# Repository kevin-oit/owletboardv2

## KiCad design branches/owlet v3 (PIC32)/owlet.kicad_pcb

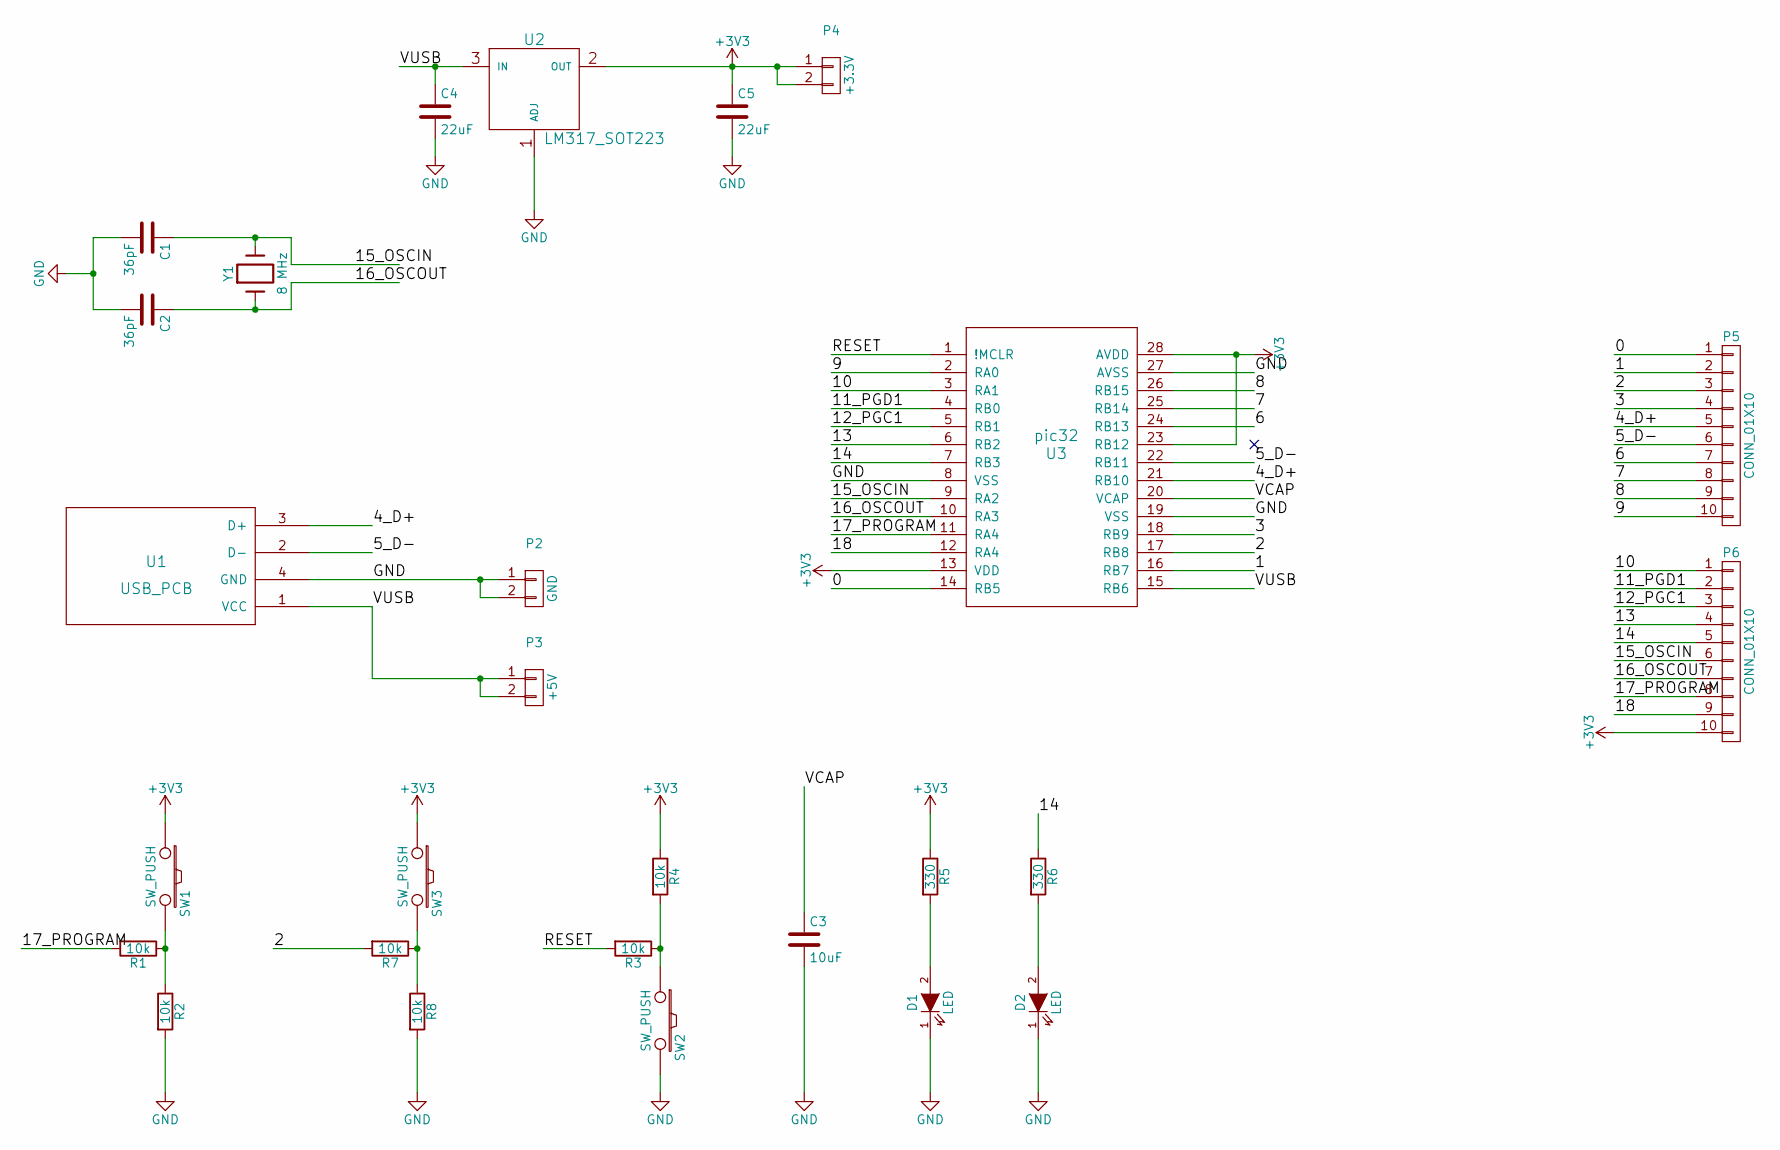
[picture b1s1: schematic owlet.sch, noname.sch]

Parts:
C1, C2: 36pF; C_Disc_D3_P2.5
C3: 10uF; C_Disc_D3_P2.5
C4, C5: 22uF; C_Disc_D3_P2.5
D1, D2: LED; LED-5MM
P2: GND; Pin_Header_Straight_1x02
P3: +5V; Pin_Header_Straight_1x02
P4: +3.3V; Pin_Header_Straight_1x02
P5, P6: CONN_01X10; Pin_Header_Straight_1x10
R1, R2, R3, R4, R7, R8: 10k; Resistor_Vertical_RM5mm
R5, R6: 330; Resistor_Vertical_RM5mm
SW1, SW2, SW3: SW_PUSH; SW_PUSH_SMALL
U1: USB_PCB; pcb_usb
U2: LM317_SOT223; SOT-223
U3: pic32; DIP-28_W7.62mm
Y1: 8 MHz; Crystal_HC49-U_Vertical

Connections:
+3V3: C5.1, P4.1, P4.2, P6.10, R4.1, R5.1, SW1.1, SW3.1, U2.2 (OUT), U3.13 (VDD), U3.23 (RB12), U3.28 (AVDD)
/0: P5.1, U3.14 (RB5)
/1: P5.2, U3.16 (RB7)
/2: P5.3, R7.2, U3.17 (RB8)
/3: P5.4, U3.18 (RB9)
/4_D+: P5.5, U1.3 (D+), U3.21 (RB10)
/5_D-: P5.6, U1.2 (D-), U3.22 (RB11)
/6: P5.7, U3.24 (RB13)
/7: P5.8, U3.25 (RB14)
/8: P5.9, U3.26 (RB15)
/9: P5.10, U3.2 (RA0)
/10: P6.1, U3.3 (RA1)
/11_PGD1: P6.2, U3.4 (RB0)
/12_PGC1: P6.3, U3.5 (RB1)
/13: P6.4, U3.6 (RB2)
/14: P6.5, R6.1, U3.7 (RB3)
/15_OSCIN: C1.1, P6.6, U3.9 (RA2), Y1.2
/16_OSCOUT: C2.1, P6.7, U3.10 (RA3), Y1.1
/17_PROGRAM: P6.8, R1.2, U3.11 (RA4)
/18: P6.9, U3.12 (RA4)
/RESET: R3.2, U3.1 (!MCLR)
/VCAP: C3.1, U3.20 (VCAP)
/VUSB: C4.1, P3.1, P3.2, U1.1 (VCC), U2.3 (IN), U3.15 (RB6)
GND: C1.2, C2.2, C3.2, C4.2, C5.2, D1.1 (K), D2.1 (K), P2.1, P2.2, R2.2, R8.2, SW2.2, U1.4 (GND), U2.1 (ADJ), U3.8 (VSS), U3.19 (VSS), U3.27 (AVSS)
unnamed: D1.2 (A), R5.2
unnamed: D2.2 (A), R6.2
unnamed: R1.1, R2.1, SW1.2
unnamed: R3.1, R4.2, SW2.1
unnamed: R7.1, R8.1, SW3.2

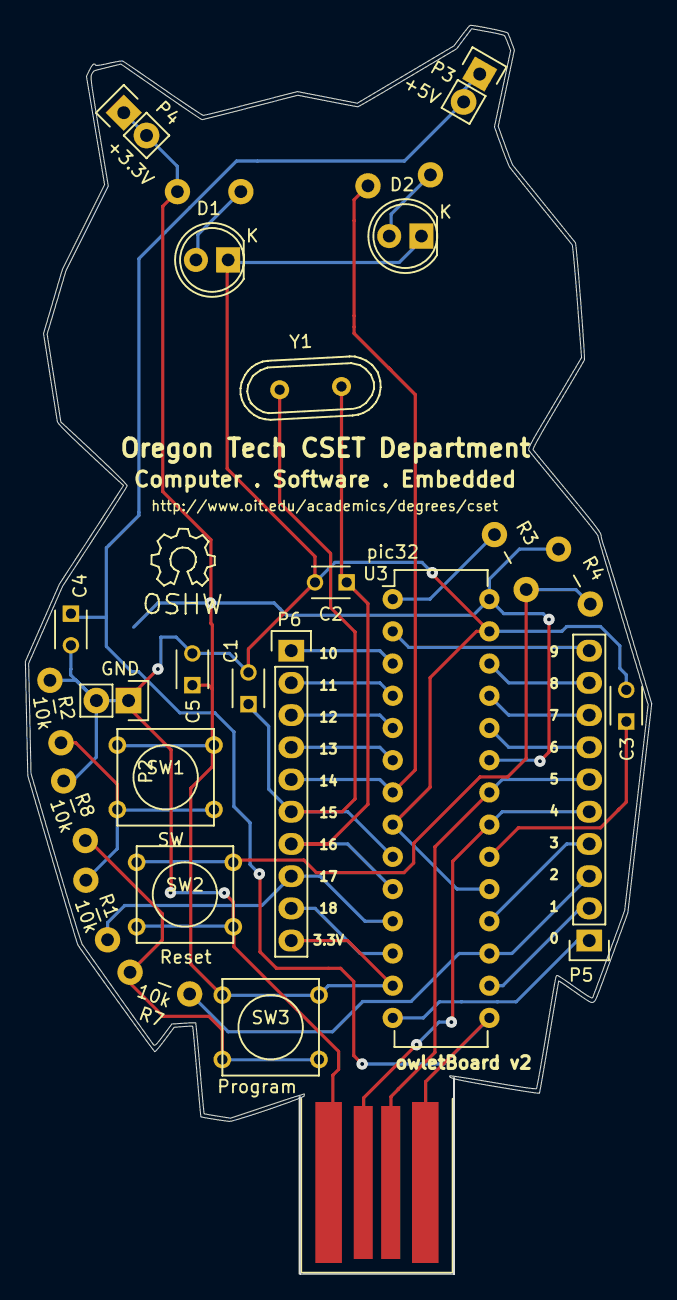
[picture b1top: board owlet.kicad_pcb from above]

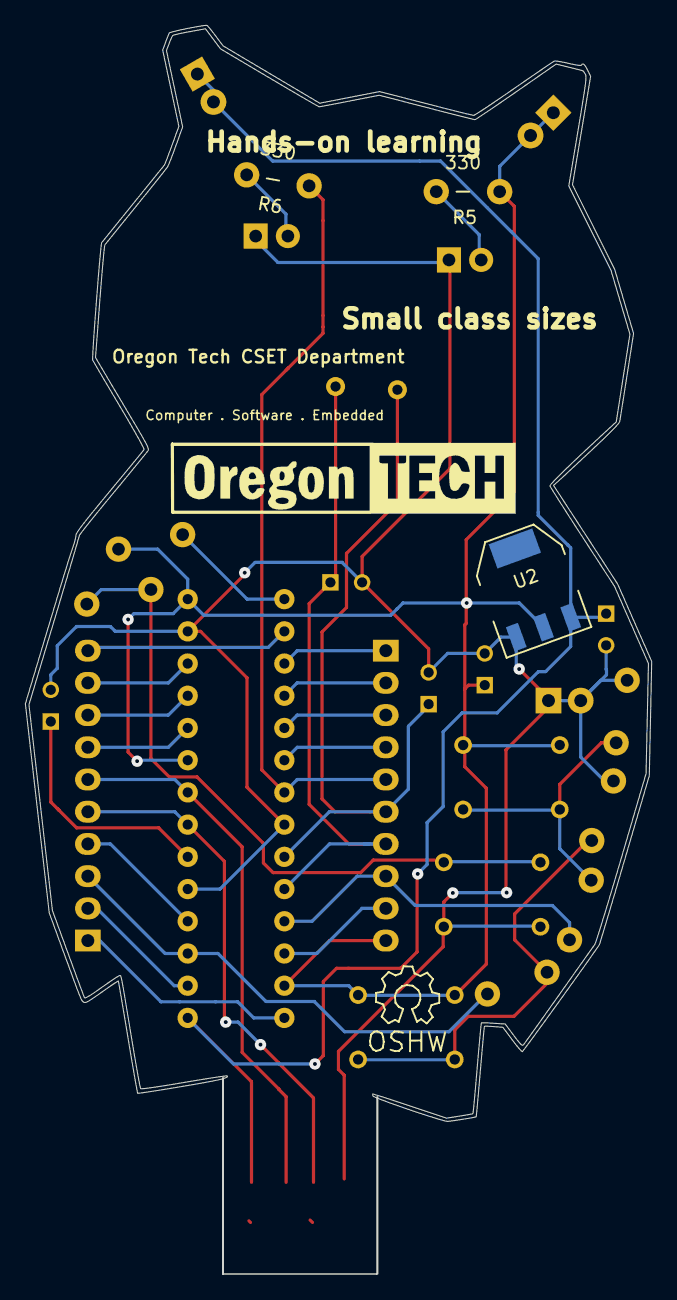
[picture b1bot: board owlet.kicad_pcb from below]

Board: 2 copper layers, 49.3 x 98.4 mm, 26 parts (3 on the bottom side), 29 nets.
